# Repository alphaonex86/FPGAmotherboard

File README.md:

# FPGAmotherboard

KiCad files of motherboards for original x86 CPUs, where an FPGA is the whole
chipset: network-virtualised hard disk, NIC, a BIOS, no VGA.

| Folder | CPU |
|---|---|
| `socket3` | AMD Am5x86-P75 |
| `socket7` | Pentium MMX (P55C) |
| `socket370` | Pentium III (Coppermine) |
| `i386` | 80386SX |

Linked project: [FPGA-CPU](https://github.com/alphaonex86/FPGA-CPU) - the other
way round, an x86 CPU in an FPGA that plugs into an original motherboard's CPU
socket.

Licence: GPL-3.0, see `LICENSE`.

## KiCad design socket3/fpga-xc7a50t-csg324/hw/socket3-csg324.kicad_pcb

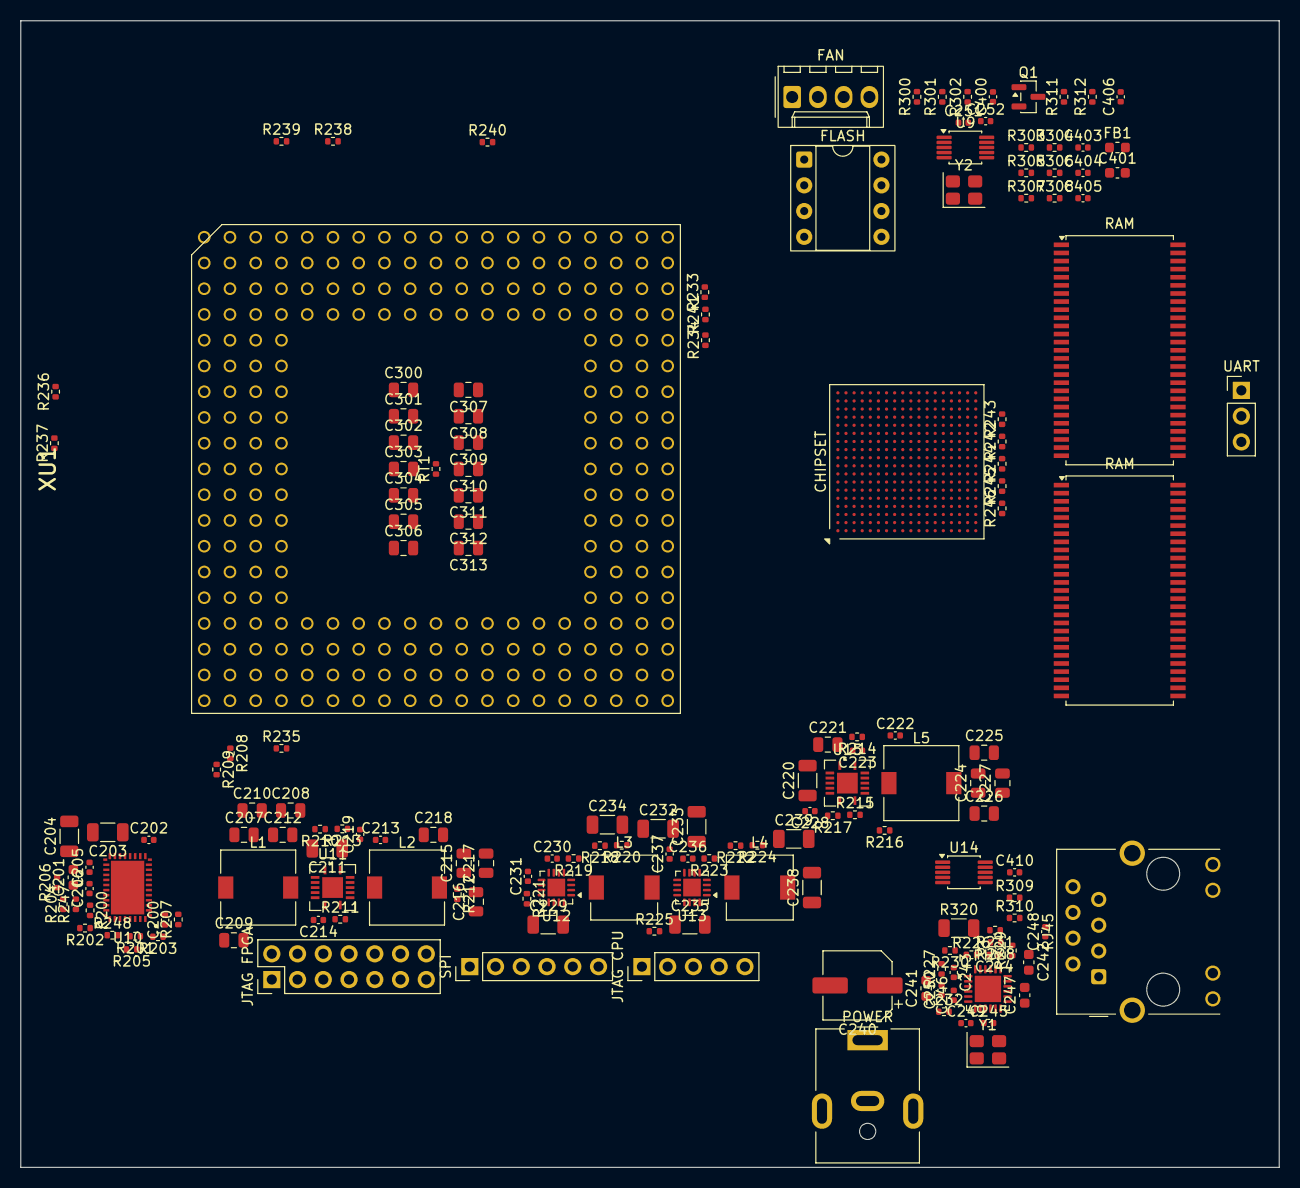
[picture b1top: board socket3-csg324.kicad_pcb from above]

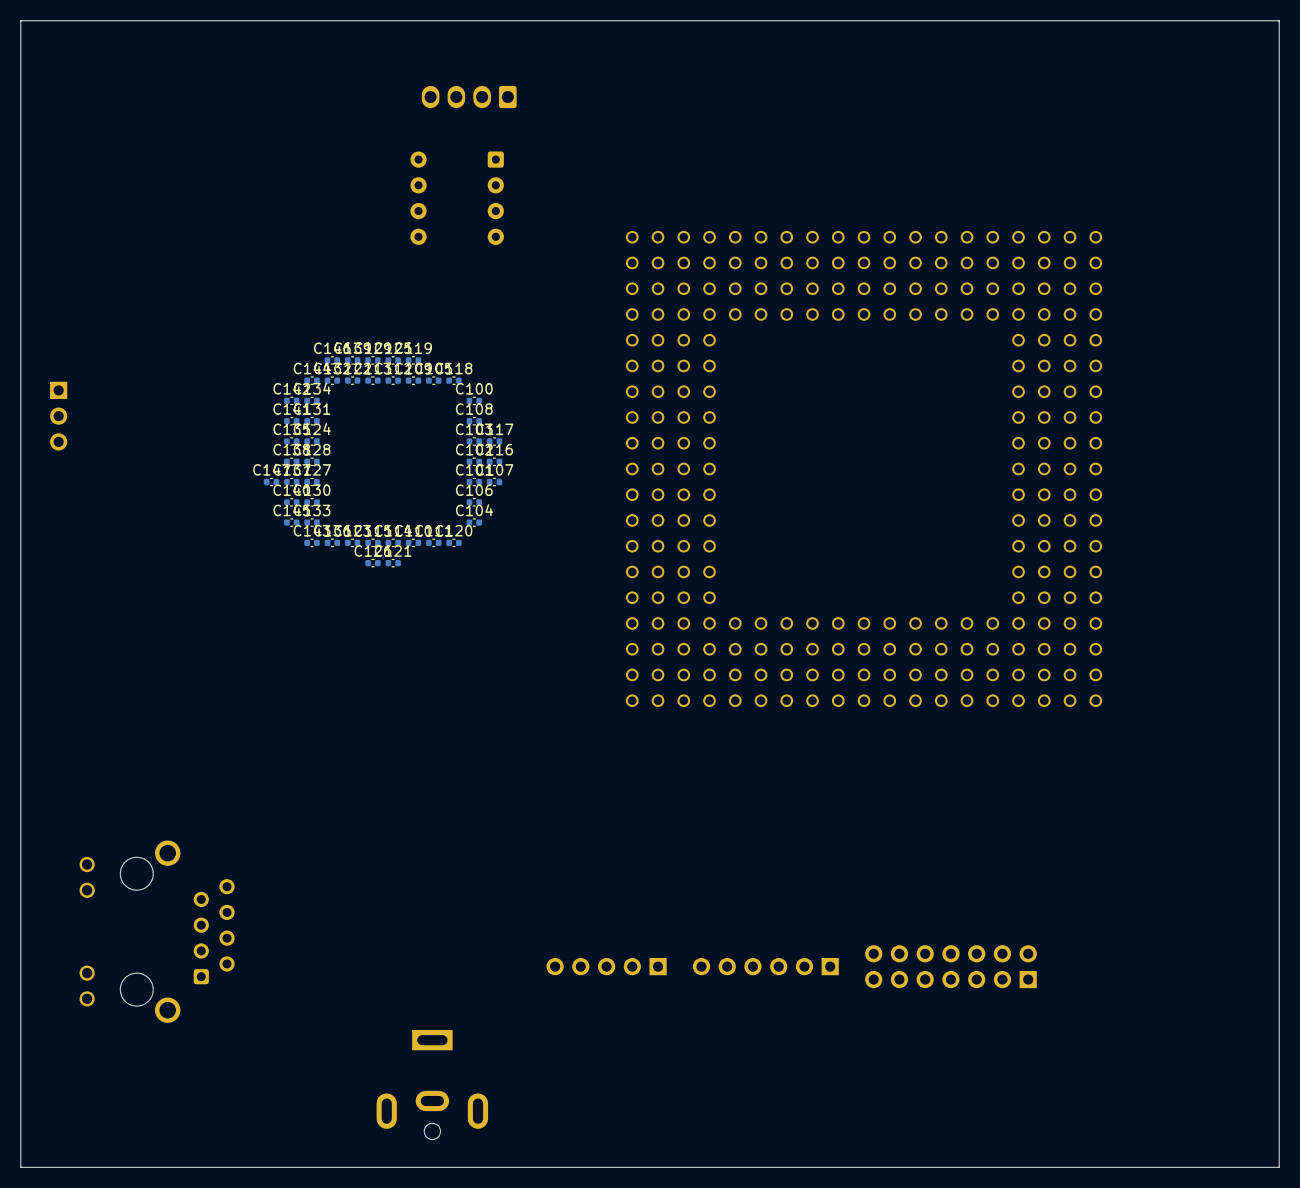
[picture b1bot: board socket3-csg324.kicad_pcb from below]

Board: 6 copper layers, 124.1 x 113.1 mm, 215 parts (48 on the bottom side), 267 nets, no tracks yet.

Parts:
C100, C101, C102, C103, C104, C105, C106, C107, C108, C109, C110, C111, C112, C113, C114, C115, C116, C117, C118, C119, C120, C121, C122, C123, C124, C125, C126, C127, C128, C129, C130, C131, C132, C133, C134, C135, C136, C137, C138, C139, C140, C141, C142, C143, C144, C145, C146, C147: 470nF; C_0402_1005Metric
C200: 1uF 16V X6S; C_0402_1005Metric
C201: 4.7uF 16V X5R; C_0603_1608Metric
C202: 100nF 16V X5R; C_0402_1005Metric
C203, C204, C211, C220, C229, C232, C233, C234, C235, C238, C239: 22uF 25V X5R; C_1206_3216Metric
C205, C214, C223, C403, C404, C405, C406: 10nF 50V X7R; C_0402_1005Metric
C206: 1uF 25V X5R; C_0402_1005Metric
C207, C208, C209, C210, C215, C216, C217, C218: 47uF 6.3V X5R; C_0805_2012Metric
C212, C221: 4.7uF 25V X7R; C_0805_2012Metric
C213, C222, C230, C236, C243, C244, C245, C248, C410: 100nF 16V X7R; C_0402_1005Metric
C219, C228: 8.2nF 50V X7R; C_0402_1005Metric
C224, C225, C226, C227: 47uF 10V X5R; C_0805_2012Metric
C231, C237: 3.3nF 50V X7R; C_0402_1005Metric
C240: 100uF 25V; CP_Elec_6.3x7.7
C241: 600R@100MHz bead; L_0603_1608Metric
C242: 10uF 10V X5R; C_0603_1608Metric
C246: 470pF 50V C0G; C_0402_1005Metric
C247: 1uF 16V X7R; C_0603_1608Metric
C249, C250: 15pF 50V C0G; C_0402_1005Metric
C251, C252: 4pF 50V C0G; C_0402_1005Metric
C300, C301, C302, C303, C304, C305, C306, C307, C308, C309, C310, C311, C312, C313: 22uF; C_0805_2012Metric
C400: 1nF 50V C0G; C_0402_1005Metric
C401: 470nF 50V X7R; C_0603_1608Metric
FB1: 600R@100MHz bead; L_0603_1608Metric
J1: HR911105A; RJ45_Hanrun_HR911105A_Horizontal
J2: SPI ISP; PinHeader_1x06_P2.54mm_Vertical
J3: PJ-063AH 12V; BarrelJack_CUI_PJ-063AH_Horizontal
J4: UART; PinHeader_1x03_P2.54mm_Vertical
J5: FPGA JTAG; PinHeader_2x07_P2.54mm_Vertical
J6: CPU JTAG; PinHeader_1x05_P2.54mm_Vertical
J7: fan 4-pin 1GND 2+12V 3TACH 4PWM; Molex_KK-254_AE-6410-04A_1x04_P2.54mm_Vertical
L1: VCORE out; L_7.3x7.3_H4.5
L2: 3V3 out; L_7.3x7.3_H4.5
L3: 1V0 out; L_6.3x6.3_H3
L4: 1V8 out; L_6.3x6.3_H3
L5: 5V out; L_7.3x7.3_H4.5
Q1: BSS138; SOT-23
R200: 10R 1%; R_0402_1005Metric
R201, R202, R205: 21.5k 1%; R_0402_1005Metric
R203: 90.9k 1%; R_0402_1005Metric
R204: 46.4k 1%; R_0402_1005Metric
R206: 4.64k 1%; R_0402_1005Metric
R207, R213, R217, R219, R223, R227, R233, R234, R235, R236, R237, R238, R239, R240, R301, R302, R303, R305, R309, R310, R311: 10k 1%; R_0402_1005Metric
R208: 1.33k 1%; R_0402_1005Metric
R209: 0R; R_0402_1005Metric
R210, R214, R220, R221, R224, R225: 100k 1%; R_0402_1005Metric
R211, R215, R300: 1.69k 1%; R_0402_1005Metric
R212: 31.6k 1%; R_0402_1005Metric
R216: 52.3k 1%; R_0402_1005Metric
R218, R308: 2.49k 1%; R_0402_1005Metric
R222: 12.4k 1%; R_0402_1005Metric
R226: 12.1k 1%; R_0402_1005Metric
R228, R229, R230, R231: 49.9 1%; R_0402_1005Metric
R232, R247: 500R 1%; R_0402_1005Metric
R241: 8.2k 1%; R_0402_1005Metric
R242, R243, R244, R248: 1k 1%; R_0402_1005Metric
R245, R246, R304, R306, R312: 4.02k 1%; R_0402_1005Metric
R307: 30.9k 1%; R_0402_1005Metric
R320: 10mR 1% 1W; R_1206_3216Metric
RT1: 10k NTC 1% B3380; R_0402_1005Metric
U2: XC7A50T-2CSG324I; Xilinx_CSG324
U3, U4: W9825G6KH-6I; TSOP-II-54_22.2x10.16mm_P0.8mm
U7: LAN8720A-CP-TR; QFN-24-1EP_4x4mm_P0.5mm_EP2.6x2.6mm
U8: W25Q64JVDAIQ (DIP-8, socketed); DIP-8_W7.62mm_Socket
U9: SI5351A-B-GTR; MSOP-10_3x3mm_P0.5mm
U10: TPS546B24ARVFR VCORE; Texas_RVF0040A_LQFN-CLIP-40_5x7mm_P0.5mm
U11: TPS54620RGYR 3V3; Texas_S-PVQFN-N14
U12: TPS62130RGTR 1V0; QFN-16-1EP_3x3mm_P0.5mm_EP1.75x1.75mm
U13: TPS62130RGTR 1V8; QFN-16-1EP_3x3mm_P0.5mm_EP1.75x1.75mm
U14: INA226AIDGSR; MSOP-10_3x3mm_P0.5mm
U15: TPS54620RGYR 5V; Texas_S-PVQFN-N14
XU1: Socket 3 ZIF 237p; Socket3_Am5x86_237
Y1, Y2: 25MHz; Crystal_SMD_3225-4Pin_3.2x2.5mm

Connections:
+1V0: C108.1, C111.1, C112.1, C115.1, C116.1, C120.1, C122.1, C123.1, C127.1, C128.1, C130.1, C131.1, C133.1, C134.1, C137.1, C138.1, C232.1, C233.1, C234.1, L3.2, R218.1, R220.1, U2.F8, U2.F10, U2.G7, U2.G9, U2.G11, U2.H8, U2.J7, U2.J11, U2.K8, U2.L7, U2.L11, U2.M8, U2.M10, U2.N7, U2.N9, U2.N11, U12.14
+1V8: C107.1, C109.1, C118.1, C124.1, C132.1, C238.1, C239.1, FB1.1, L4.2, R222.1, R224.1, U2.E8, U2.F12, U2.H12, U2.K12, U2.M12, U13.14
+1V8_ADC: C117.1, C401.1, FB1.2, U2.H10
+3V3: C100.1, C101.1, C102.1, C103.1, C104.1, C105.1, C106.1, C110.1, C113.1, C114.1, C119.1, C121.1, C125.1, C126.1, C129.1, C135.1, C136.1, C139.1, C140.1, C141.1, C142.1, C143.1, C144.1, C145.1, C146.1, C147.1, C215.1, C216.1, C217.1, C218.1, C241.1, C245.1, C410.1, J2.1, J5.2, L2.2, R207.1, R212.1, R242.2, R245.2, R246.2, R301.2, R305.1, R309.2, R310.2, R311.1, U2.A7, U2.A17, U2.B10, U2.C3, U2.C13, U2.D6, U2.D16, U2.F2, U2.G5, U2.G15, U2.H18, U2.J1, U2.K4, U2.K14, U2.L15, U2.L17, U2.N3, U2.N13, U2.P6, U2.P8, U2.P16, U2.R9, U2.T2, U2.T12, U2.U5, U2.U15, U2.V8, U2.V18, U3.1, U3.3, U3.9, U3.14, U3.27, U3.43, U3.49, U4.1, U4.3, U4.9, U4.14, U4.27, U4.43, U4.49, U7.9, U8.8, U9.1, U9.7, U14.6
+5V: C224.1, C225.1, C226.1, C227.1, C229.1, C230.1, C235.1, C236.1, L5.2, R216.1, R221.1, R225.1, U12.10, U12.11, U12.12, U13.10, U13.11, U13.12
+12V: C203.1, C204.1, C205.1, C211.1, C212.1, C220.1, C221.1, C240.1, J7.2, R200.1, R307.1, R320.2, U10.22, U10.23, U10.24, U10.25, U11.4, U11.5, U11.6, U14.8, U14.9, U15.4, U15.5, U15.6
+12V_IN: J3.1, R320.1, U14.10
GND: C100.2, C101.2, C102.2, C103.2, C104.2, C105.2, C106.2, C107.2, C108.2, C109.2, C110.2, C111.2, C112.2, C113.2, C114.2, C115.2, C116.2, C117.2, C118.2, C119.2, C120.2, C121.2, C122.2, C123.2, C124.2, C125.2, C126.2, C127.2, C128.2, C129.2, C130.2, C131.2, C132.2, C133.2, C134.2, C135.2, C136.2, C137.2, C138.2, C139.2, C140.2, C141.2, C142.2, C143.2, C144.2, C145.2, C146.2, C147.2, C201.2, C203.2, C204.2, C205.2, C206.2, C207.2, C208.2, C209.2, C210.2, C211.2, C212.2, C214.2, C215.2, C216.2, C217.2, C218.2, C219.2, C220.2, C221.2, C223.2, C224.2, C225.2, C226.2, C227.2, C228.2, C229.2, C230.2, C231.2, C232.2, C233.2, C234.2, C235.2, C236.2, C237.2, C238.2, C239.2, C240.2, C242.2, C243.2, C244.2, C245.2, C246.2, C247.2, C248.2, C249.2, C250.2, C251.2, C252.2, C300.2, C301.2, C302.2, C303.2, C304.2, C305.2, C306.2, C307.2, C308.2, C309.2, C310.2, C311.2, C312.2, C313.2, C400.2, C401.2, C403.2, C404.2, C405.2, C406.2, C410.2, J1.8, J1.SH, J2.2, J3.2, J4.1, J5.1, J5.3, J5.5, J5.7, J5.9, J5.11, J5.13, J6.5, J7.1, Q1.2, R202.2, R204.2, R206.2, R209.1, R210.2, R213.2, R214.2, R217.2, R219.2, R223.2, R226.2, R227.2, R239.2, R243.2, R244.2, R247.2, R302.2, R304.2, R306.2, R308.2, R312.2, RT1.2, U2.A2, U2.A12, U2.A18, U2.B5, U2.B12, U2.B14, U2.B15, U2.C8, U2.C14, U2.C18, U2.D1, U2.D11, U2.E4, U2.E14, U2.F7, U2.F9, U2.F11, U2.F17, U2.G8, U2.G10, U2.G12, U2.H3, U2.H7, U2.H9, U2.H11, U2.H13, U2.J6, U2.J8, U2.J9, U2.J10, U2.J12, U2.J16, U2.K7, U2.K9, U2.K10, U2.K11, U2.L2, U2.L8, U2.L12, U2.M5, U2.M7, U2.M9, U2.M11, U2.M15, U2.N8, U2.N10, U2.N12, U2.N18, U2.P1, U2.R4, U2.R14, U2.T7, U2.T17, U2.U10, U2.V3, U2.V13, U3.6, U3.12, U3.28, U3.41, U3.46, U3.52, U3.54, U4.6, U4.12, U4.28, U4.41, U4.46, U4.52, U4.54, U7.25, U8.4, U9.8, U10.6, U10.13, U10.14, U10.15, U10.16, U10.17, U10.18, U10.19, U10.20, U10.21, U10.36, U10.37, U10.41, U11.2, U11.3, U11.15, U12.6, U12.15, U12.16, U12.17, U13.6, U13.15, U13.16, U13.17, U14.1, U14.2, U14.7, U15.2, U15.3, U15.15, XU1.A7 (VSS), XU1.A9 (VSS), XU1.A11 (VSS), XU1.B3 (VSS), XU1.B4 (VSS), XU1.B5 (VSS), XU1.E1 (VSS), XU1.E17 (VSS), XU1.G1 (VSS), XU1.G17 (VSS), XU1.H1 (VSS), XU1.H17 (VSS), XU1.K1 (VSS), XU1.K17 (VSS), XU1.L1 (VSS), XU1.L17 (VSS), XU1.M1 (VSS), XU1.M17 (VSS), XU1.P17 (VSS), XU1.Q2 (VSS), XU1.R4 (VSS), XU1.R17 (CLKMUL), XU1.S6 (VSS), XU1.S8 (VSS), XU1.S9 (VSS), XU1.S10 (VSS), XU1.S11 (VSS), XU1.S12 (VSS), XU1.S14 (VSS), Y1.2, Y1.4, Y2.2, Y2.4
VCORE: C207.1, C208.1, C209.1, C210.1, C300.1, C301.1, C302.1, C303.1, C304.1, C305.1, C306.1, C307.1, C308.1, C309.1, C310.1, C311.1, C312.1, C313.1, L1.2, R208.1, R233.2, R234.2, R235.2, R236.2, R237.2, R238.2, R240.2, R241.2, R303.1, XU1.B7 (VCC), XU1.B9 (VCC), XU1.B11 (VCC), XU1.C4 (VCC), XU1.C5 (VCC), XU1.E2 (VCC), XU1.E16 (VCC), XU1.G2 (VCC), XU1.G16 (VCC), XU1.H16 (VCC), XU1.K2 (VCC), XU1.K16 (VCC), XU1.L16 (VCC), XU1.M2 (VCC), XU1.M16 (VCC), XU1.P16 (VCC), XU1.R3 (VCC), XU1.R6 (VCC), XU1.R8 (VCC), XU1.R9 (VCC), XU1.R10 (VCC), XU1.R11 (VCC), XU1.R14 (VCC)
cpu_a20m_n: U2.A13, XU1.D15 (A20M)
cpu_a[2]: U2.A3, XU1.Q14 (A2)
cpu_a[3]: U2.D2, XU1.R15 (A3)
cpu_a[4]: U2.H1, XU1.S16 (A4)
cpu_a[5]: U2.H4, XU1.Q12 (A5)
cpu_a[6]: U2.G1, XU1.S15 (A6)
cpu_a[7]: U2.J4, XU1.Q13 (A7)
cpu_a[8]: U2.C2, XU1.R13 (A8)
cpu_a[9]: U2.G4, XU1.Q11 (A9)
cpu_a[10]: U2.F1, XU1.S13 (A10)
cpu_a[11]: U2.B2, XU1.R12 (A11)
cpu_a[12]: U2.E1, XU1.S7 (A12)
cpu_a[13]: U2.F4, XU1.Q10 (A13)
cpu_a[14]: U2.C1, XU1.S5 (A14)
cpu_a[15]: U2.J3, XU1.R7 (A15)
cpu_a[16]: U2.D4, XU1.Q9 (A16)
cpu_a[17]: U2.F5, XU1.Q3 (A17)
cpu_a[18]: U2.G3, XU1.R5 (A18)
cpu_a[19]: U2.H5, XU1.Q4 (A19)
cpu_a[20]: U2.C4, XU1.Q8 (A20)
cpu_a[21]: U2.J5, XU1.Q5 (A21)
cpu_a[22]: U2.B4, XU1.Q7 (A22)
cpu_a[23]: U2.J2, XU1.S3 (A23)
cpu_a[24]: U2.A4, XU1.Q6 (A24)
cpu_a[25]: U2.F3, XU1.R2 (A25)
cpu_a[26]: U2.H2, XU1.S2 (A26)
cpu_a[27]: U2.G2, XU1.S1 (A27)
cpu_a[28]: U2.E3, XU1.R1 (A28)
cpu_a[29]: U2.A5, XU1.P2 (A29)
cpu_a[30]: U2.C5, XU1.P3 (A30)
cpu_a[31]: U2.E5, XU1.Q1 (A31)
cpu_ads_n: U2.K1, XU1.S17 (ADS)
cpu_ahold: U2.G17, XU1.A17 (AHOLD)
cpu_be_n[0]: U2.D8, XU1.K15 (BE0)
cpu_be_n[1]: U2.D9, XU1.J16 (BE1)
cpu_be_n[2]: U2.C9, XU1.J15 (BE2)
cpu_be_n[3]: U2.B11, XU1.F17 (BE3)
cpu_blast_n: U2.E2, XU1.R16 (BLAST)
cpu_boff_n: U2.D13, XU1.D17 (BOFF)
cpu_brdy_n: U2.D10, XU1.H15 (BRDY)
cpu_breq: U2.B3, XU1.Q15 (BREQ)
cpu_bs8_n: R234.1, XU1.D16 (BS8)
cpu_bs16_n: R233.1, XU1.C17 (BS16)
cpu_cache_n: U2.E16, XU1.B12 (CACHE)
cpu_clk: U9.10, XU1.C3 (CLK)
cpu_d[0]: U2.H6, XU1.P1 (D0)
cpu_d[1]: U2.C6, XU1.N2 (D1)
cpu_d[2]: U2.B6, XU1.N1 (D2)
cpu_d[3]: U2.C10, XU1.H2 (D3)
cpu_d[4]: U2.E7, XU1.M3 (D4)
cpu_d[5]: U2.A9, XU1.J2 (D5)
cpu_d[6]: U2.B7, XU1.L2 (D6)
cpu_d[7]: U2.C7, XU1.L3 (D7)
cpu_d[8]: U2.J13, XU1.F2 (D8)
cpu_d[9]: U2.G14, XU1.D1 (D9)
cpu_d[10]: U2.F13, XU1.E3 (D10)
cpu_d[11]: U2.K16, XU1.C1 (D11)
cpu_d[12]: U2.C11, XU1.G3 (D12)
cpu_d[13]: U2.H14, XU1.D2 (D13)
cpu_d[14]: U2.B8, XU1.K3 (D14)
cpu_d[15]: U2.K13, XU1.F3 (D15)
cpu_d[16]: U2.B9, XU1.J3 (D16)
cpu_d[17]: U2.J14, XU1.D3 (D17)
cpu_d[18]: U2.A15, XU1.C2 (D18)
cpu_d[19]: U2.H17, XU1.B1 (D19)
cpu_d[20]: U2.D18, XU1.A1 (D20)
cpu_d[21]: U2.J17, XU1.B2 (D21)
cpu_d[22]: U2.E18, XU1.A2 (D22)
cpu_d[23]: U2.F18, XU1.A4 (D23)
cpu_d[24]: U2.G18, XU1.A6 (D24)
cpu_d[25]: U2.A16, XU1.B6 (D25)
cpu_d[26]: U2.D15, XU1.C7 (D26)
cpu_d[27]: U2.C15, XU1.C6 (D27)
cpu_d[28]: U2.E15, XU1.C8 (D28)
cpu_d[29]: U2.J18, XU1.A8 (D29)
cpu_d[30]: U2.F15, XU1.C9 (D30)
cpu_d[31]: U2.B16, XU1.B8 (D31)
cpu_dc_n: U2.A6, XU1.M15 (D_C)
cpu_dp[0]: R235.1, XU1.N3 (DP0)
cpu_dp[1]: R236.1, XU1.F1 (DP1)
cpu_dp[2]: R237.1, XU1.H3 (DP2)
cpu_dp[3]: R238.1, XU1.A5 (DP3)
cpu_eads_n: U2.H16, XU1.B17 (EADS)
cpu_ferr_n: U2.K15, XU1.C14 (FERR)
cpu_flush_n: U2.A14, XU1.C15 (FLUSH)
cpu_hitm_n: U2.C17, XU1.A12 (HITM)
cpu_hlda: U2.D5, XU1.P15 (HLDA)
cpu_hold: U2.G13, XU1.E15 (HOLD)
cpu_ignne_n: U2.D17, XU1.A15 (IGNNE)
cpu_intr: U2.E17, XU1.A16 (INTR)
cpu_inv: U2.B17, XU1.A10 (INV)
cpu_ken_n: U2.D12, XU1.F15 (KEN)
cpu_lock_n: U2.E6, XU1.N15 (LOCK)
cpu_mio_n: U2.F6, XU1.N16 (M_IO)
cpu_nmi: U2.G16, XU1.B15 (NMI)
cpu_pcd: U2.A8, XU1.J17 (PCD)
cpu_plock_n: U2.D3, XU1.Q16 (PLOCK)
cpu_pwt: U2.D7, XU1.L15 (PWT)
cpu_rdy_n: U2.A11, XU1.F16 (RDY)
cpu_reset: R241.1, U2.F14, XU1.C16 (RESET)
cpu_smi_n: U2.C16, XU1.B10 (SMI)
cpu_smiact_n: U2.J15, XU1.C12 (SMIACT)
cpu_sreset: U2.H15, XU1.C10 (SRESET)
cpu_stpclk_n: U2.A10, XU1.G15 (STPCLK)
cpu_tck: J6.1, R239.1, XU1.A3 (TCK)
cpu_tdi: J6.3, XU1.A14 (TDI)
cpu_tdo: J6.4, XU1.B16 (TDO)
cpu_tms: J6.2, XU1.B14 (TMS)
cpu_up_n: R240.1, XU1.C11 (UP)
cpu_voldet: U2.B1, XU1.S4 (VOLDET)
cpu_wbwt_n: U2.F16, XU1.B13 (WB_WT)
cpu_wr_n: U2.G6, XU1.N17 (W_R)
en_vcore: R247.1, U2.A1, U10.27
eth_mdc: U2.L4, U7.13
eth_mdi_rxn: J1.6, R231.1, U7.22
eth_mdi_rxp: J1.3, R230.1, U7.23
eth_mdi_txn: J1.2, R229.1, U7.20
eth_mdi_txp: J1.1, R228.1, U7.21
eth_mdio: U2.L1, U7.12
eth_nintsel: R227.1, U7.2
eth_rbias: R226.1, U7.24
eth_ref_clk: U2.N5, U7.14
eth_rmii_crs_dv: U2.M3, U7.11
eth_rmii_rx_er: U2.L3, U7.10
eth_rmii_rxd[0]: U2.K3, U7.8
eth_rmii_rxd[1]: U2.M4, U7.7
eth_rmii_tx_en: U2.M6, U7.16
eth_rmii_txd[0]: U2.L6, U7.17
eth_rmii_txd[1]: U2.K6, U7.18
eth_rst_n: U2.K5, U7.15
eth_vdda: C241.2, C242.1, C243.1, C244.1, C248.1, J1.4, J1.5, R228.2, R229.2, R230.2, R231.2, U7.1, U7.19
eth_vddcr: C246.1, C247.1, U7.6
eth_xtal1: C249.1, U7.5, Y1.1
eth_xtal2: C250.1, R232.1, Y1.3
eth_xtal2_drv: R232.2, U7.4
fan_pwm: J7.4, Q1.3
fan_pwm_g: Q1.1, R302.1, U2.V17
fan_tach: J7.3, R300.1, R301.1
fan_tach_f: C400.1, R300.2, U2.V16
fpga_init_b: R246.1, U2.P7
fpga_m0: R242.1, U2.P12
fpga_m1: R243.1, U2.P13
fpga_m2: R244.1, U2.P11
fpga_program_b: R245.1, U2.P9
fpga_refclk: U2.P15, U9.9
i2c_scl: R309.1, U2.V14, U9.4, U10.3, U14.5
i2c_sda: R310.1, U2.V12, U9.5, U10.2, U14.4
jtag_tck: J5.6, U2.E10
jtag_tdi: J5.10, U2.E11
jtag_tdo: J5.8, U2.E13
jtag_tms: J5.4, U2.E12
sdram_a[0]: U2.R3, U3.23, U4.23
sdram_a[1]: U2.N2, U3.24, U4.24
sdram_a[2]: U2.R2, U3.25, U4.25
sdram_a[3]: U2.R1, U3.26, U4.26
sdram_a[4]: U2.T1, U3.29, U4.29
sdram_a[5]: U2.N1, U3.30, U4.30
sdram_a[6]: U2.P2, U3.31, U4.31
sdram_a[7]: U2.T3, U3.32, U4.32
sdram_a[8]: U2.P3, U3.33, U4.33
sdram_a[9]: U2.P4, U3.34, U4.34
sdram_a[10]: U2.T4, U3.22, U4.22
sdram_a[11]: U2.T5, U3.35, U4.35
sdram_a[12]: U2.P5, U3.36, U4.36
sdram_ba[0]: U2.R5, U3.20, U4.20
sdram_ba[1]: U2.N4, U3.21, U4.21
sdram_cas_n: U2.T8, U3.17, U4.17
sdram_cke: U2.T6, U3.37, U4.37
sdram_clk: U2.R7, U3.38, U4.38
sdram_cs_n: U2.L5, U3.19, U4.19
sdram_dq[0]: U2.R18, U3.2
sdram_dq[1]: U2.U18, U3.4
sdram_dq[2]: U2.T16, U3.5
sdram_dq[3]: U2.T15, U3.7
sdram_dq[4]: U2.U14, U3.8
sdram_dq[5]: U2.U13, U3.10
sdram_dq[6]: U2.T11, U3.11
sdram_dq[7]: U2.V11, U3.13
sdram_dq[8]: U2.T10, U3.42
sdram_dq[9]: U2.U11, U3.44
sdram_dq[10]: U2.U12, U3.45
sdram_dq[11]: U2.T13, U3.47
sdram_dq[12]: U2.T14, U3.48
sdram_dq[13]: U2.U16, U3.50
sdram_dq[14]: U2.U17, U3.51
sdram_dq[15]: U2.T18, U3.53
sdram_dq[16]: U2.U9, U4.2
sdram_dq[17]: U2.U8, U4.4
sdram_dq[18]: U2.V7, U4.5
sdram_dq[19]: U2.U6, U4.7
sdram_dq[20]: U2.V5, U4.8
sdram_dq[21]: U2.V4, U4.10
sdram_dq[22]: U2.M2, U4.11
sdram_dq[23]: U2.V2, U4.13
sdram_dq[24]: U2.M1, U4.42
sdram_dq[25]: U2.U2, U4.44
sdram_dq[26]: U2.U3, U4.45
sdram_dq[27]: U2.U4, U4.47
sdram_dq[28]: U2.V6, U4.48
sdram_dq[29]: U2.N6, U4.50
sdram_dq[30]: U2.U7, U4.51
sdram_dq[31]: U2.V9, U4.53
sdram_dqm[0]: U2.V10, U3.15
sdram_dqm[1]: U2.T9, U3.39
sdram_dqm[2]: U2.U1, U4.15
sdram_dqm[3]: U2.V1, U4.39
sdram_ras_n: U2.R6, U3.18, U4.18
sdram_we_n: U2.R8, U3.16, U4.16
spi_clk: J2.4, U2.E9, U8.6
spi_cs_n: J2.3, U2.L13, U8.1
spi_dq0: J2.6, U2.K17, U8.5
spi_dq1: J2.5, U2.K18, U8.2
spi_dq2: U2.L14, U8.3
spi_dq3: U2.M14, U8.7
sw_1v0: L3.1, U12.1, U12.2, U12.3
sw_1v8: L4.1, U13.1, U13.2, U13.3
sw_3v3: C213.2, L2.1, U11.11, U11.12
sw_5v: C222.2, L5.1, U15.11, U15.12
sw_vcore: C202.2, L1.1, U10.8, U10.9, U10.10, U10.11, U10.12
tsen_socket: C406.1, R311.2, R312.1, RT1.1, U2.B13
u9_xa: C251.1, U9.2, Y2.1
u9_xb: C252.1, U9.3, Y2.3
u10_avin: C206.1, R200.2, U10.26
u10_boot: C202.1, U10.7
u10_bp1v5: C200.1, R201.1, R203.1, R205.1, U10.4
u10_drtn: C200.2, U10.5
u10_msel1: R201.2, R202.1, U10.32
u10_msel2: R203.2, R204.1, U10.29
u10_pgood: R207.2, U10.1
u10_vdd5: C201.1, U10.28
u10_vsel: R205.2, R206.1, U10.30
u11_boot: C213.1, U11.13
u11_comp: R211.1, U11.8
u11_compz: C219.1, R211.2
u11_fb: R212.2, R213.1, U11.7
u11_rt: R210.1, U11.1
u11_ss: C214.1, U11.9
u12_en: R221.2, U12.13
u12_fb: R218.2, R219.1, U12.5
u12_pg: R220.2, U12.4
u12_ss: C231.1, U12.9
u13_en: R225.2, U13.13
u13_fb: R222.2, R223.1, U13.5
u13_pg: R224.2, U13.4
u13_ss: C237.1, U13.9
u15_boot: C222.1, U15.13
u15_comp: R215.1, U15.8
u15_compz: C228.1, R215.2
u15_fb: R216.2, R217.1, U15.7
u15_rt: R214.1, U15.1
u15_ss: C223.1, U15.9
uart_rx: J4.2, U2.R15
uart_tx: J4.3, U2.R13
vcore_gsense: R209.2, R248.2, U10.34
vcore_sense: R208.2, R248.1, U10.33
vsen_3v3: C404.1, R305.2, R306.1, U2.C12
vsen_12v: C405.1, R307.2, R308.1, U2.B18
vsen_vcore: C403.1, R303.2, R304.1, U2.D14
